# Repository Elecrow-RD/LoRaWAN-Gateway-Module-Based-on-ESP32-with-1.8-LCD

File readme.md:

### 1, Product picture

### 2, Product version number

|      | Hardware | Software | Remark |
| ---- | -------- | -------- | ------ |
| 1    | V1.0     | V1.0     | latest |

### 3, product information

- | Main Processor Chip              | ESP32 WROOM32 with dual-core 32-bit LX6 microprocessor from Xtensa @ 240MHz |
  | -------------------------------- | ------------------------------------------------------------ |
  | LoRa RF transceiver module       | RA-01H                                                       |
  | RA-01H Supports frequency band   | 803MHZ-930MHZ                                                |
  | RA-01H Support modulation method | FSK、GFSK、MSK、LoRa                                         |
  | Channel                          | Single channel                                               |
  | Support Lorawan protocol         | Support Lorawan 1.0.3                                        |
  | WiFi Antenna                     | SMA 2.4G WiFi Antenna                                        |
  | Communication distance           | Obstructed state: up to 1 kmUnobstructed state: up to 1.8 kilometers |
  | Development environment          | Arduino/Micropython                                          |
  | Interface and function           | 1x USB-C interface,1x Ethernet Interface,1x Boot Button,1x Reset Button,2x Indicator Lights. |
  | Working input voltage            | USB DC-5V                                                    |
  | Operating Temperature            | -10°C ~ 65°C                                                 |
  | Dimensions                       | 65mm(L)x58mm(W)                                              |

### 4,Quick Start

##### Arduino IDE starts

1.Download the library files used by this product to the 'libraries' folder.

C:\Users\Documents\Arduino\libraries\

2.Open the Arduino IDE

3.Open the code configuration environment and burn it

### 5,Folder structure.

|--Datasheet: Includes datasheets for components used in the project, providing detailed specifications, electrical characteristics, and pin configurations.

|--Eagle_SCH&PCB: Contains **Eagle CAD** schematic (`.sch`) and PCB layout (`.brd`) files. These are used for circuit design and PCB manufacturing.

|--example: Provides example code and projects to demonstrate how to use the hardware and libraries. These examples help users get started quickly.

|--factory_firmware: Stores pre-compiled factory firmware that can be directly flashed onto the device. This ensures the device runs the default functionality.

|--factory_sourcecode: Contains the source code for the factory firmware, allowing users to modify and rebuild the firmware as needed.

### 6,Pin definition

**IO port definition**

| GPIO0  | BOOT        | GPIO1  | TXD0      | GPIO2  | RXD0      |
| ------ | ----------- | ------ | --------- | ------ | --------- |
| GPIO3  | RXD0        | GPIO4  | LCD_DC    | GPIO5  | DATA      |
| GPIO6  | NC          | GPIO7  | NC        | GPIO8  | NC        |
| GPIO9  | NC          | GPIO10 | NC        | GPIO11 | NC        |
| GPIO12 | RA_RST      | GPIO13 | RA_DIO1   | GPIO14 | RA_NSS    |
| GPIO15 | XP_CS       | GPIO16 | LCD_BLK   | GPIO17 | RMII_CLK  |
| GPIO18 | ETH_MDIO    | GPIO19 | RMII_TXD0 | GPIO20 | NC        |
| GPIO21 | RMII_TX_EN  | GPIO22 | RMII_TXD1 | GPIO23 | ETH_MDC   |
| GPIO24 | NC          | GPIO25 | RMII_RXD0 | GPIO26 | RMII_RXD1 |
| GPIO27 | RMII_CRS_DV | GPIO28 | NC        | GPIO29 | NC        |
| GPIO30 | NC          | GPIO31 | NC        | GPIO32 | MOSI      |
| GPIO33 | SCK         | GPIO34 | RA_BUSY   | GPIO35 | MISO      |
| GPIO36 | NC          | GPIO37 | NC        | GPIO38 | C         |
| GPIO39 | PEN         |        |           |        |           |

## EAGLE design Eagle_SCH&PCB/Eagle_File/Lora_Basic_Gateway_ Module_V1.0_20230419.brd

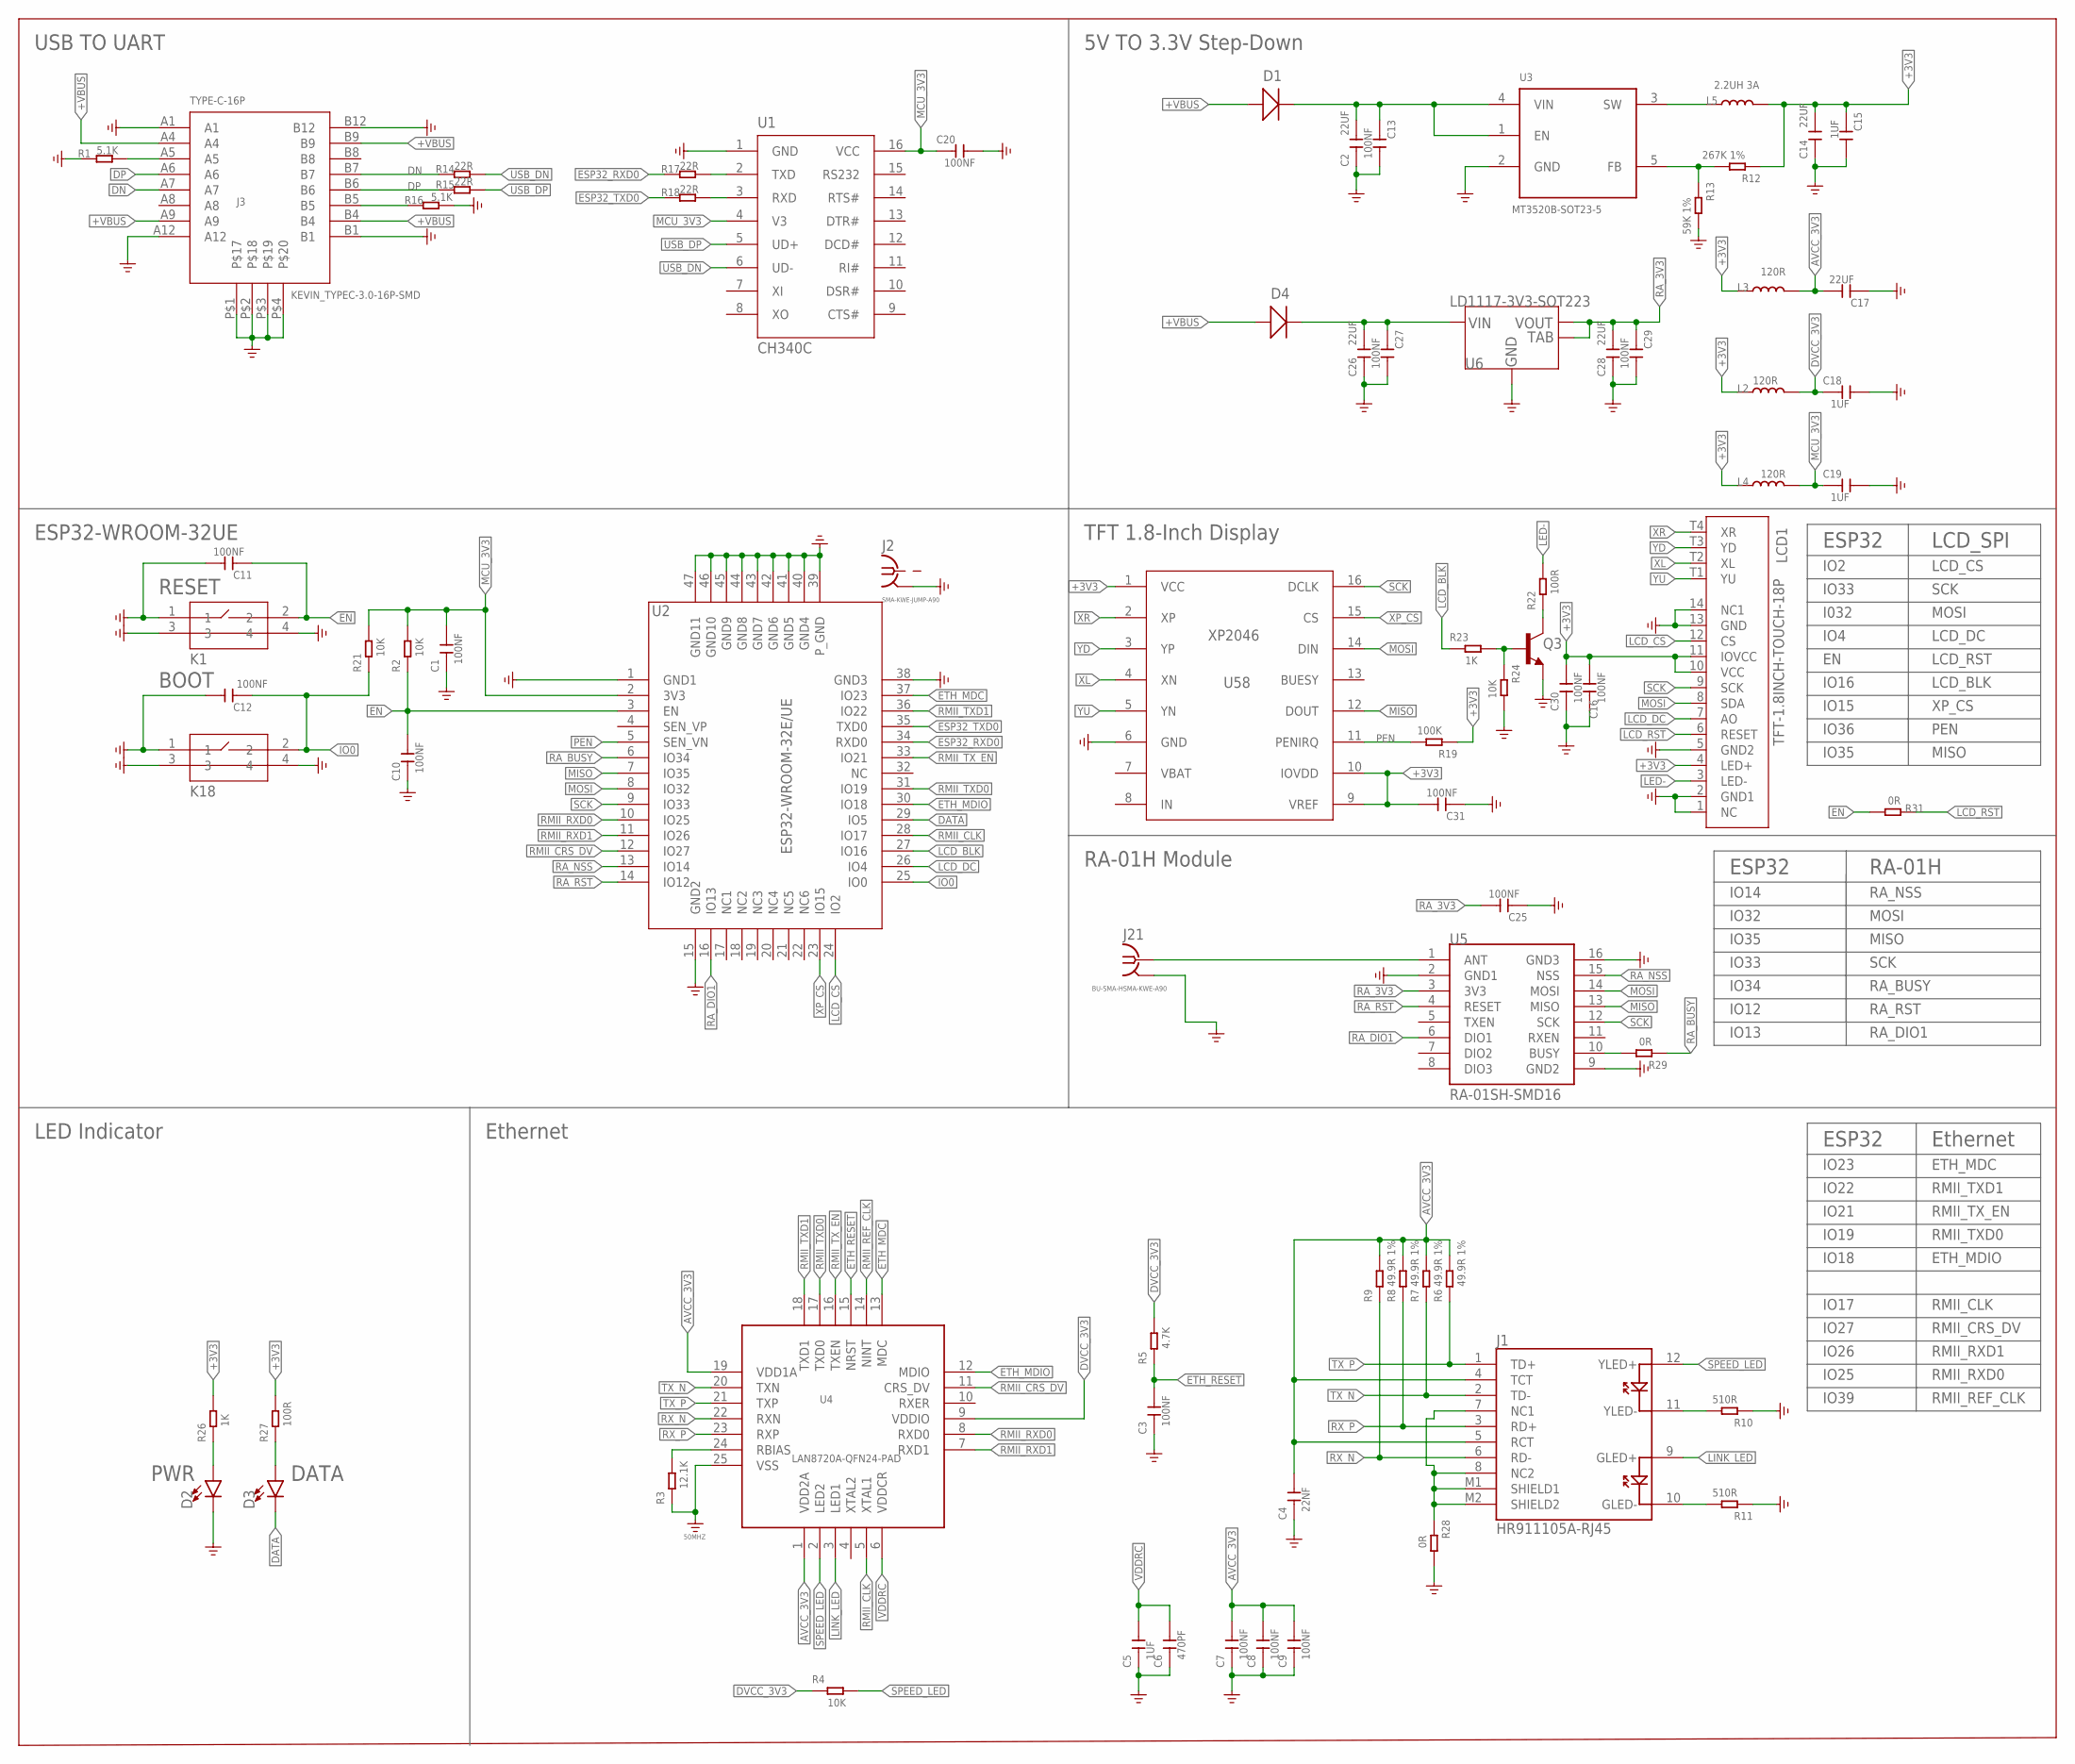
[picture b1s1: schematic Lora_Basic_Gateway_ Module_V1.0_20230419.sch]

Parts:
C1, C3, C7, C8, C9, C10, C11, C12, C13, C16, C20, C25, C27, C29, C30, C31: 100NF; C0603
C2, C14, C17, C26, C28: 22UF; C0805
C4: 22NF; C0603
C5, C15, C18, C19: 1UF; C0603
C6: 470PF; C0603
D1, D4: DIODEB130L-13-F; SMA
D2, D3: LED; LED-F3MM-DIP2-A90
J1: HR911105A-RJ45
J2: SMA-KWE-JUMP-A90
J3: KEVIN_TYPEC-3.0-16P-SMD; KEVIN_3.0TYPEC-SMD
J21: BU-SMA-HSMA-KWE-A90; SMA-KWE-A90
K1, K18: KEY_666MM_DIPA90; KEY_6*6*6MM_DIPA90
L2, L4: 120R; L0805
L3: 120R; L0603
L5: 2.2UH 3A; L0420
LCD1: TFT-1.8INCH-TOUCH-18P; TFT-1.8INCH-TOUCH-18P-SMD
Q3: 600mA/40V; SOT23-3
R1, R16: 5.1K; R0603
R2, R4, R21, R24: 10K; R0603
R3: 12.1K; R0603
R5: 4.7K; R0603
R6, R7, R8, R9: 49.9R 1%; R0603
R10, R11: 510R; R0603
R12: 267K 1%; R0603
R13: 59K 1%; R0603
R14, R15, R17, R18: 22R; R0603
R19: 100K; R0603
R22, R27: 100R; R0603
R23, R26: 1K; R0603
R28, R29, R31: 0R; R0603
U1: CH340C; SOP-16
U2: ESP32-WROOM-32E/UE; ESP32-WROOM-32UE
U3: MT3520B-SOT23-5; IC_SOT23-5
U4: LAN8720A-QFN24-PAD; QFN24-PAD
U5: RA-01SH-SMD16
U6: LD1117-3V3-SOT223; SOT223
U58: XP2046; XP2046-SSOP16

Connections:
+3V3: C14.2, C15.1, C16.2, C30.2, C31.2, L2.1, L3.1, L4.1, L5.2, LCD1.4 (LED+), LCD1.10 (VCC), LCD1.11 (IOVCC), R12.1, R19.1, R26.2, R27.2, U58.1 (VCC), U58.9 (VREF), U58.10 (IOVDD)
+VBUS: D1.2 (+), D4.2 (+), J3.A4, J3.A9, J3.B4, J3.B9
AVCC_3V3: C4.2, C7.2, C8.2, C9.2, C17.2, J1.4 (TCT), J1.5 (RCT), L3.2, R6.2, R7.2, R8.2, R9.2, U4.1 (VDD2A), U4.19 (VDD1A)
DATA: D3.K (C), U2.29 (IO5)
DN: J3.A7, J3.B7, R14.1
DP: J3.A6, J3.B6, R15.1
DVCC_3V3: C18.1, L2.2, R4.1, R5.2, U4.9 (VDDIO)
EN: C10.2, C11.1, K1.2, R2.1, R31.2, U2.3 (EN)
ESP32_RXD0: R17.1, U2.34 (RXD0)
ESP32_TXD0: R18.1, U2.35 (TXD0)
ETH_MDC: U2.37 (IO23), U4.13 (MDC)
ETH_MDIO: U2.30 (IO18), U4.12 (MDIO)
ETH_RESET: C3.2, R5.1, U4.15 (NRST)
GND: C1.1, C2.1, C3.1, C4.1, C5.1, C6.1, C7.1, C8.1, C9.1, C10.1, C11.2, C12.2, C13.2, C14.1, C15.2, C16.1, C17.1, C18.2, C19.2, C20.2, C25.1, C26.1, C27.2, C28.1, C29.2, C30.1, C31.1, D2.K (C), J2.2, J2.3, J2.4, J2.5, J3.A1, J3.A12, J3.B1, J3.B12, J3.P$1, J3.P$2, J3.P$3, J3.P$4, J21.2, J21.3 (2), J21.4 (2), J21.5 (2), K1.1, K1.3, K1.4, K18.1, K18.3, K18.4, LCD1.1 (NC), LCD1.2 (GND1), LCD1.5 (GND2), LCD1.13 (GND), LCD1.14 (NC1), Q3.2 (E), R1.1, R3.1, R10.1, R11.1, R13.2, R16.2, R24.2, R28.2, U1.1 (GND), U2.1 (GND1), U2.15 (GND2), U2.38 (GND3), U2.39 (P_GND), U2.40 (GND4), U2.41 (GND5), U2.42 (GND6), U2.43 (GND7), U2.44 (GND8), U2.45 (GND9), U2.46 (GND10), U2.47 (GND11), U3.2 (GND), U4.25 (VSS), U5.2 (GND1), U5.9 (GND2), U5.16 (GND3), U6.1 (GND), U58.6 (GND)
IO0: C12.1, K18.2, R21.1, U2.25 (IO0)
LCD_BLK: R23.1, U2.27 (IO16)
LCD_CS: LCD1.12 (CS), U2.24 (IO2)
LCD_DC: LCD1.7 (AO), U2.26 (IO4)
LCD_RST: LCD1.6 (RESET), R31.1
LED-: LCD1.3 (LED-), R22.2
LINK_LED: J1.9 (GLED+), U4.3 (LED1)
MCU_3V3: C1.2, C19.1, C20.1, L4.2, R2.2, R21.2, U1.4 (V3), U1.16 (VCC), U2.2 (3V3)
MISO: U2.7 (IO35), U5.13 (MISO), U58.12 (DOUT)
MOSI: LCD1.8 (SDA), U2.8 (IO32), U5.14 (MOSI), U58.14 (DIN)
unnamed: Q3.3 (C), R22.1
unnamed: D2.A, R26.1
unnamed: D3.A, R27.1
unnamed: C26.2, C27.1, D4.1 (-), U6.3 (VIN)
unnamed: R29.2, U5.10 (BUSY)
unnamed: J1.7 (NC1), J1.8 (NC2), J1.M1 (SHIELD1), J1.M2 (SHIELD2), R28.1
unnamed: Q3.1 (B), R23.2, R24.1
unnamed: J1.10 (GLED-), R11.2
unnamed: J21.1, U5.1 (ANT)
unnamed: J1.11 (YLED-), R10.2
unnamed: C2.2, C13.1, D1.1 (-), U3.1 (EN), U3.4 (VIN)
unnamed: R12.2, R13.1, U3.5 (FB)
unnamed: R3.2, U4.24 (RBIAS)
unnamed: L5.1, U3.3 (SW)
unnamed: J3.B5, R16.1
unnamed: J3.A5, R1.2
unnamed: R17.2, U1.2 (TXD)
unnamed: R18.2, U1.3 (RXD)
PEN: R19.2, U2.5 (SEN_VN), U58.11 (PENIRQ)
RA_3V3: C25.2, C28.2, C29.1, U5.3 (3V3), U6.2 (VOUT), U6.4 (TAB)
RA_BUSY: R29.1, U2.6 (IO34)
RA_DIO1: U2.16 (IO13), U5.6 (DIO1)
RA_NSS: U2.13 (IO14), U5.15 (NSS)
RA_RST: U2.14 (IO12), U5.4 (RESET)
RMII_CLK: U2.28 (IO17), U4.5 (XTAL1)
RMII_CRS_DV: U2.12 (IO27), U4.11 (CRS_DV)
RMII_REF_CLK: U4.14 (NINT)
RMII_RXD0: U2.10 (IO25), U4.8 (RXD0)
RMII_RXD1: U2.11 (IO26), U4.7 (RXD1)
RMII_TXD0: U2.31 (IO19), U4.17 (TXD0)
RMII_TXD1: U2.36 (IO22), U4.18 (TXD1)
RMII_TX_EN: U2.33 (IO21), U4.16 (TXEN)
RX_N: J1.6 (RD-), R9.1, U4.22 (RXN)
RX_P: J1.3 (RD+), R8.1, U4.23 (RXP)
SCK: LCD1.9 (SCK), U2.9 (IO33), U5.12 (SCK), U58.16 (DCLK)
SPEED_LED: J1.12 (YLED+), R4.2, U4.2 (LED2)
TX_N: J1.2 (TD-), R7.1, U4.20 (TXN)
TX_P: J1.1 (TD+), R6.1, U4.21 (TXP)
USB_DN: R14.2, U1.6 (UD-)
USB_DP: R15.2, U1.5 (UD+)
VDDRC: C5.2, C6.2, U4.6 (VDDCR)
XL: LCD1.T2 (XL), U58.4 (XN)
XP_CS: U2.23 (IO15), U58.15 (CS)
XR: LCD1.T4 (XR), U58.2 (XP)
YD: LCD1.T3 (YD), U58.3 (YP)
YU: LCD1.T1 (YU), U58.5 (YN)

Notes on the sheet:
ESP32
Ethernet
ETH_MDC
RMII_TXD1
RMII_TX_EN
RMII_TXD0
ETH_MDIO
RMII_CLK
RMII_CRS_DV
RMII_RXD1
RMII_RXD0
IO23
IO22
IO21
IO19
IO18
IO17
IO27
IO26
IO25
LCD_SPI
LCD_CS
SCK
MOSI
LCD_DC
LCD_RST
LCD_BLK
IO2
IO33
I032
IO4
IO16
RA-01H
RA_NSS
MISO
RA_BUSY
RA_RST
IO14
IO32
IO35

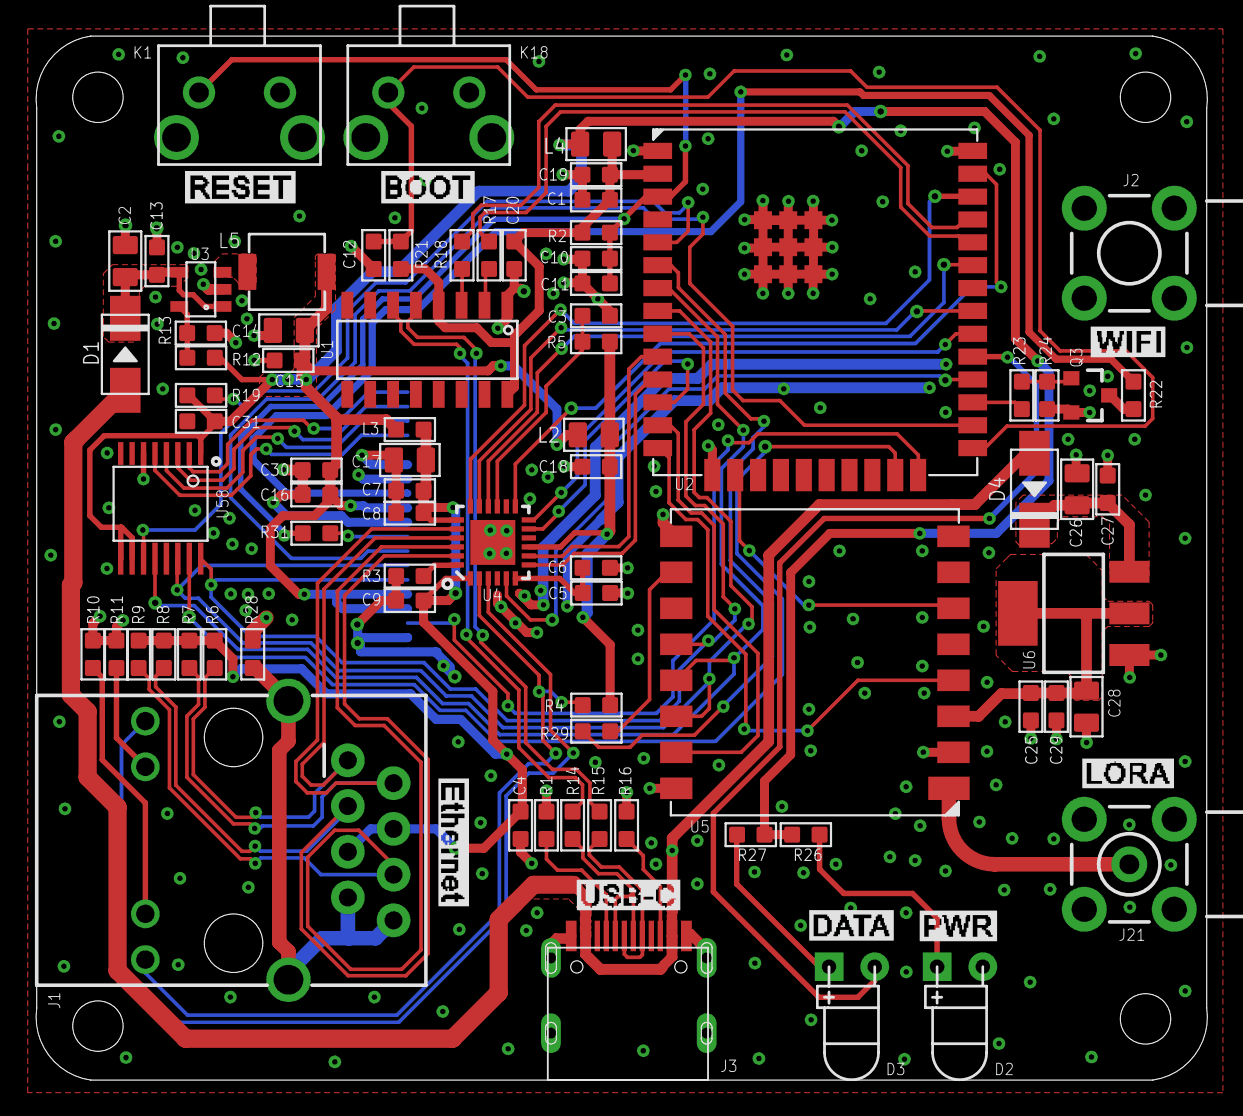
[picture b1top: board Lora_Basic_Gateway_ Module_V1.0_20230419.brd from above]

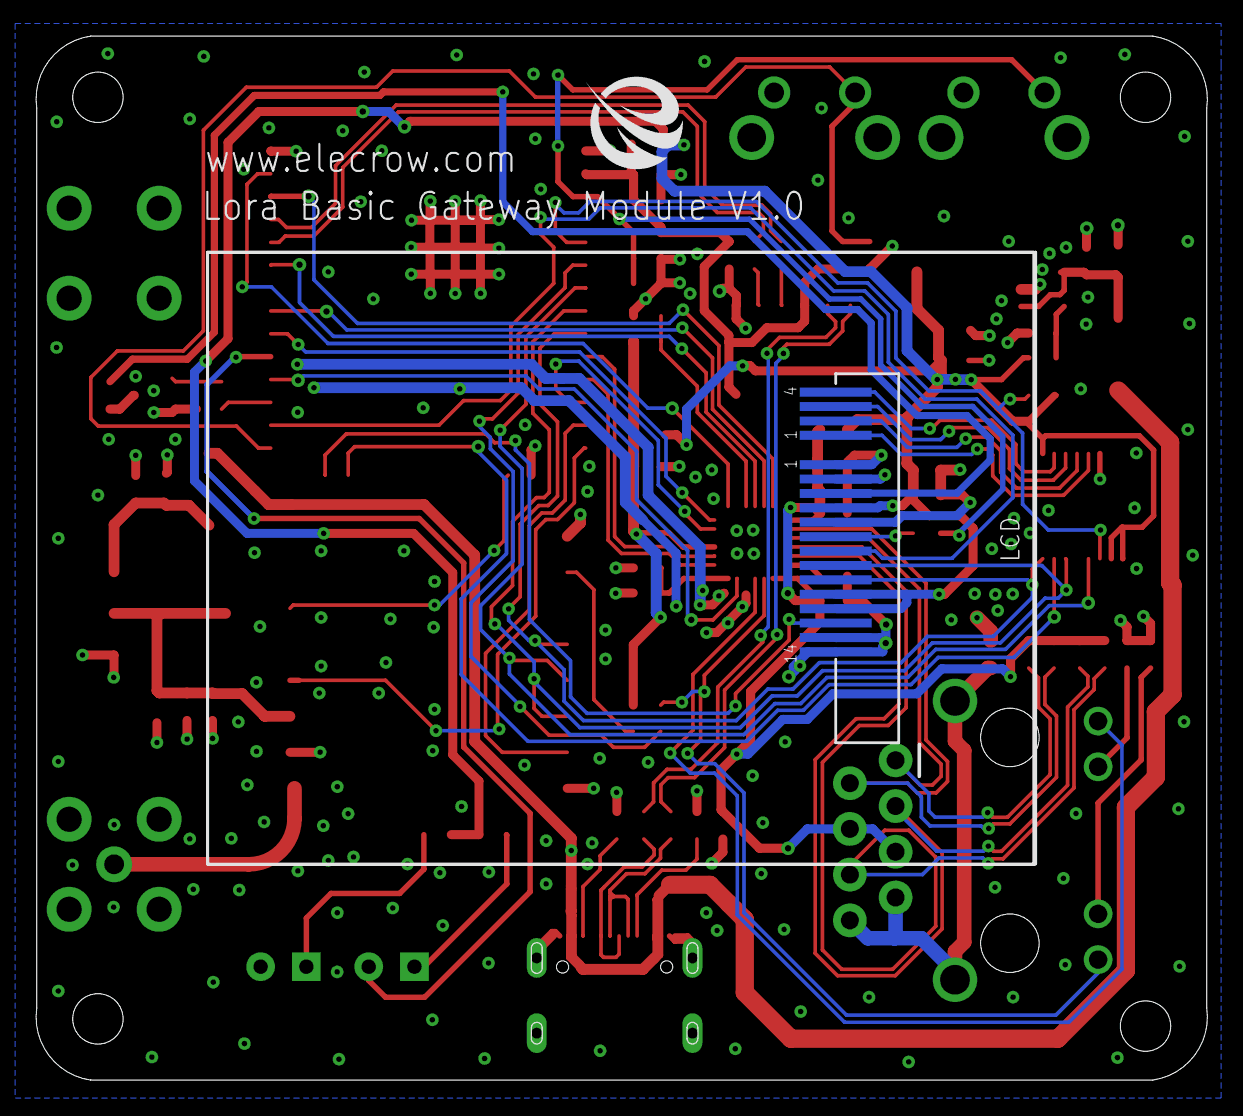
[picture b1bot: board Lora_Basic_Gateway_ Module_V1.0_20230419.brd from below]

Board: 2 copper layers, 65.1 x 58.0 mm, 79 parts (2 on the bottom side), 69 nets.

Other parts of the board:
U$160: ELECROW-NEW
